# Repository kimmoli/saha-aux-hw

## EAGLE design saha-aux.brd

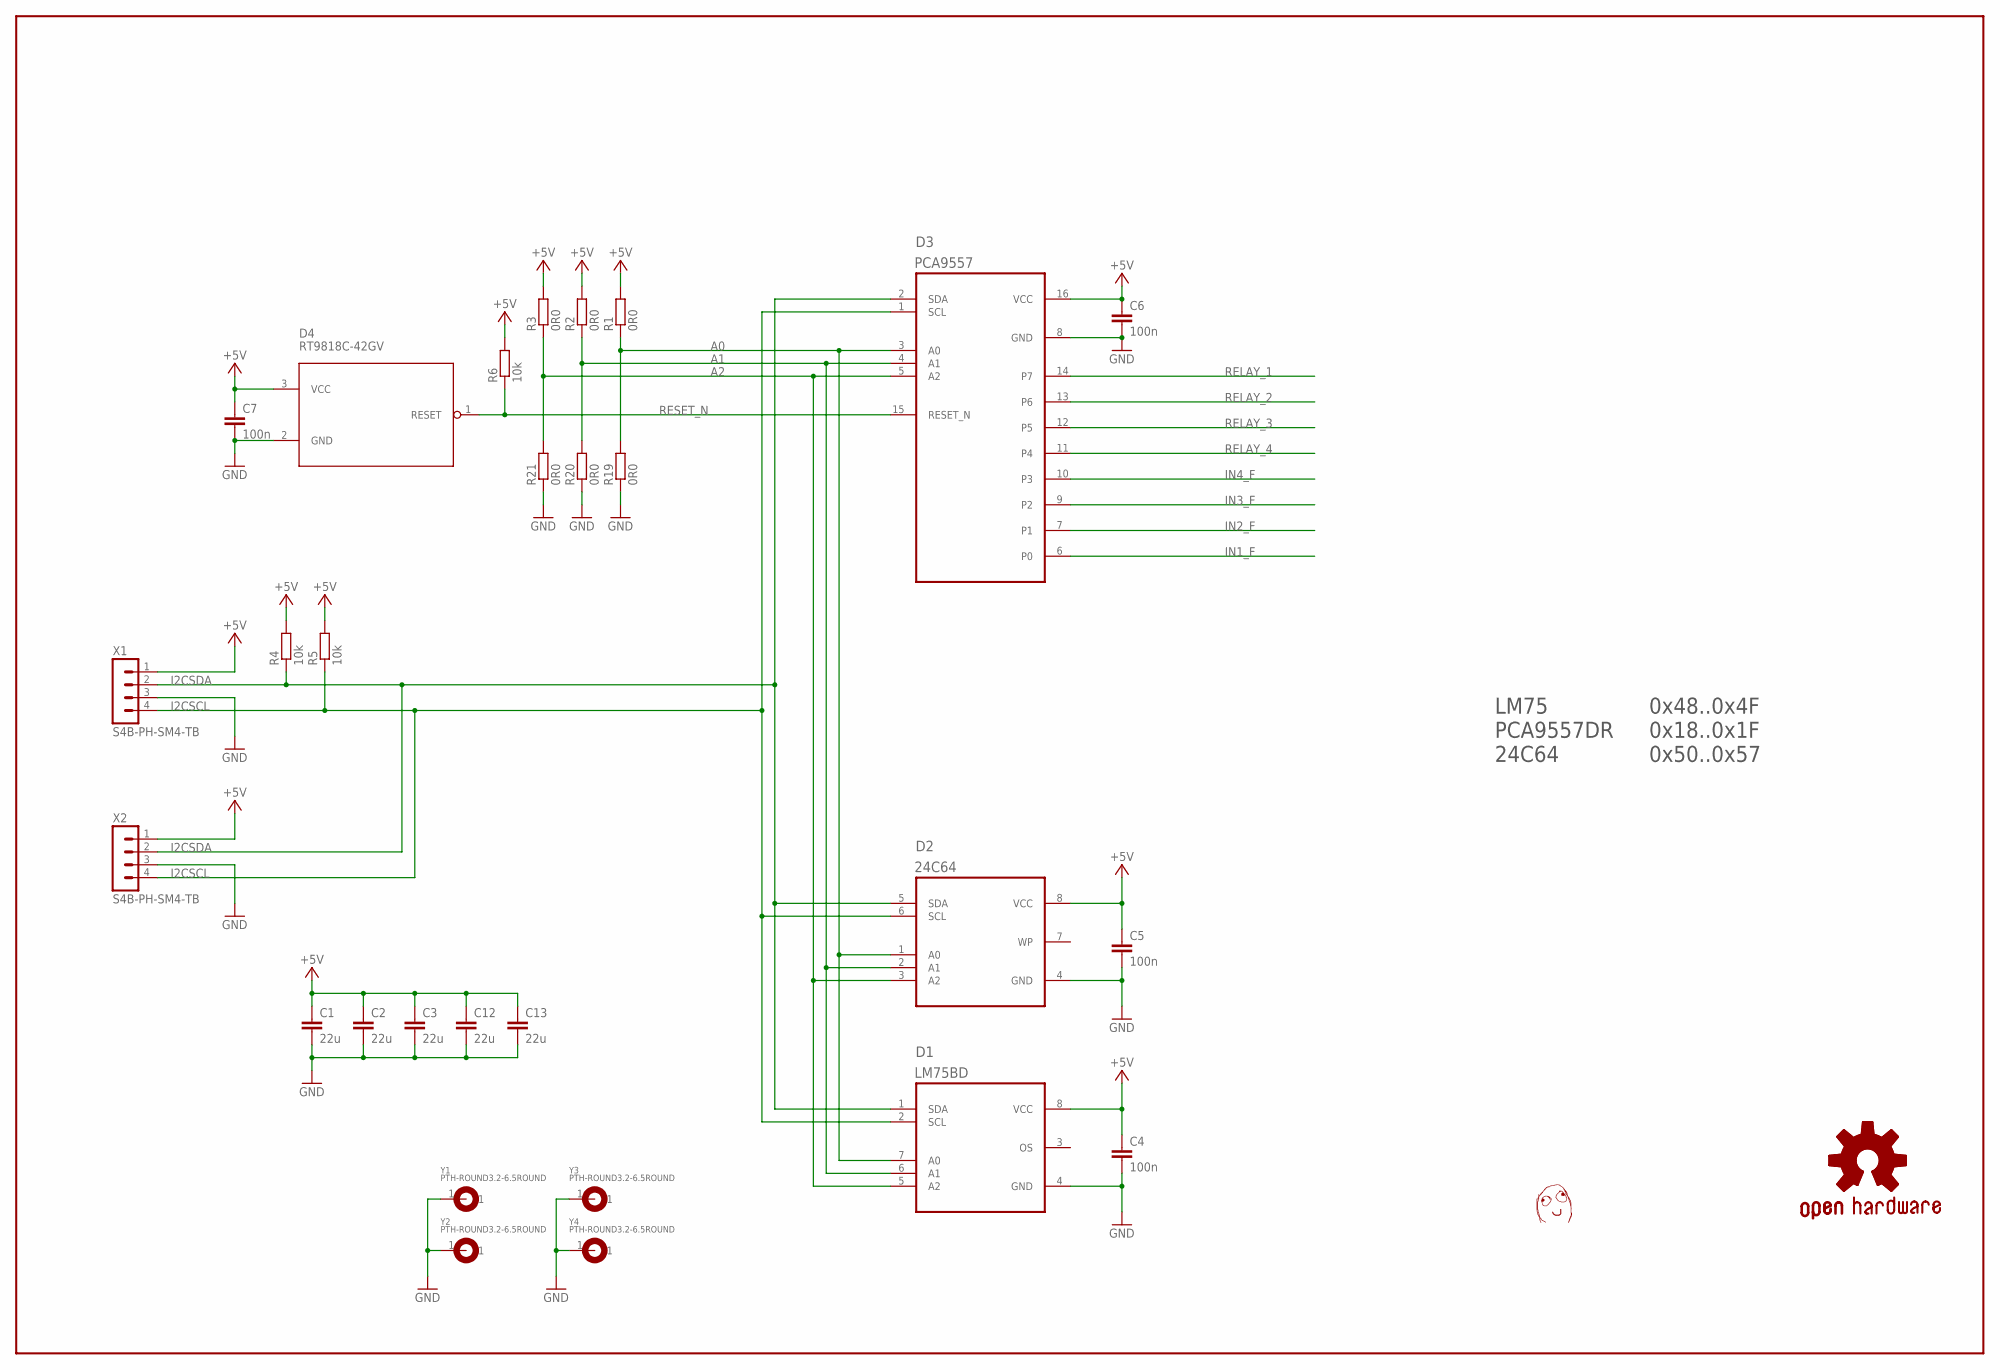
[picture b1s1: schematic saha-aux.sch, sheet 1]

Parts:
C1, C2, C3, C12, C13: 22u; C0805
C4, C5, C6, C7: 100n; C0603
D1: LM75BD; SOIC8-N
D2: 24C64; SOIC8-N
D3: PCA9557; SOIC16-N
D4: RT9818C-42GV; SOT23
R1, R2, R3, R19, R20, R21: 0R0; R0603
R4, R5, R6: 10k; R0603
U$1: DAFUG
X1, X2: S4B-PH-SM4-TB; JST-PH2.0-RA-4
Y1, Y2, Y3, Y4: PTH-ROUND3.2-6.5ROUND; EKE_PTH-3.2-6.5

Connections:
+5V: C1.1, C2.1, C3.1, C4.1, C5.1, C6.1, C7.1, C12.1, C13.1, D1.8 (VCC), D2.8 (VCC), D3.16 (VCC), D4.3 (VCC), R1.2, R2.2, R3.2, R4.2, R5.2, R6.2, X1.1, X2.1; also elsewhere on the board
A0: D1.7 (A0), D2.1 (A0), D3.3 (A0), R1.1, R19.2
A1: D1.6 (A1), D2.2 (A1), D3.4 (A1), R2.1, R20.2
A2: D1.5 (A2), D2.3 (A2), D3.5 (A2), R3.1, R21.2
GND: C1.2, C2.2, C3.2, C4.2, C5.2, C6.2, C7.2, C12.2, C13.2, D1.4 (GND), D2.4 (GND), D3.8 (GND), D4.2 (GND), R19.1, R20.1, R21.1, X1.3, X2.3, Y1.1, Y2.1, Y3.1, Y4.1; also elsewhere on the board
I2CSCL: D1.2 (SCL), D2.6 (SCL), D3.1 (SCL), R5.1, X1.4, X2.4
I2CSDA: D1.1 (SDA), D2.5 (SDA), D3.2 (SDA), R4.1, X1.2, X2.2
IN1_F: D3.6 (P0); also elsewhere on the board
IN2_F: D3.7 (P1); also elsewhere on the board
IN3_F: D3.9 (P2); also elsewhere on the board
IN4_F: D3.10 (P3); also elsewhere on the board
RELAY_1: D3.14 (P7); also elsewhere on the board
RELAY_2: D3.13 (P6); also elsewhere on the board
RELAY_3: D3.12 (P5); also elsewhere on the board
RELAY_4: D3.11 (P4); also elsewhere on the board
RESET_N: D3.15 (RESET_N), D4.1 (RESET), R6.1

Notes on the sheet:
LM75 PCA9557DR 24C64
0x48..0x4F 0x18..0x1F 0x50..0x57

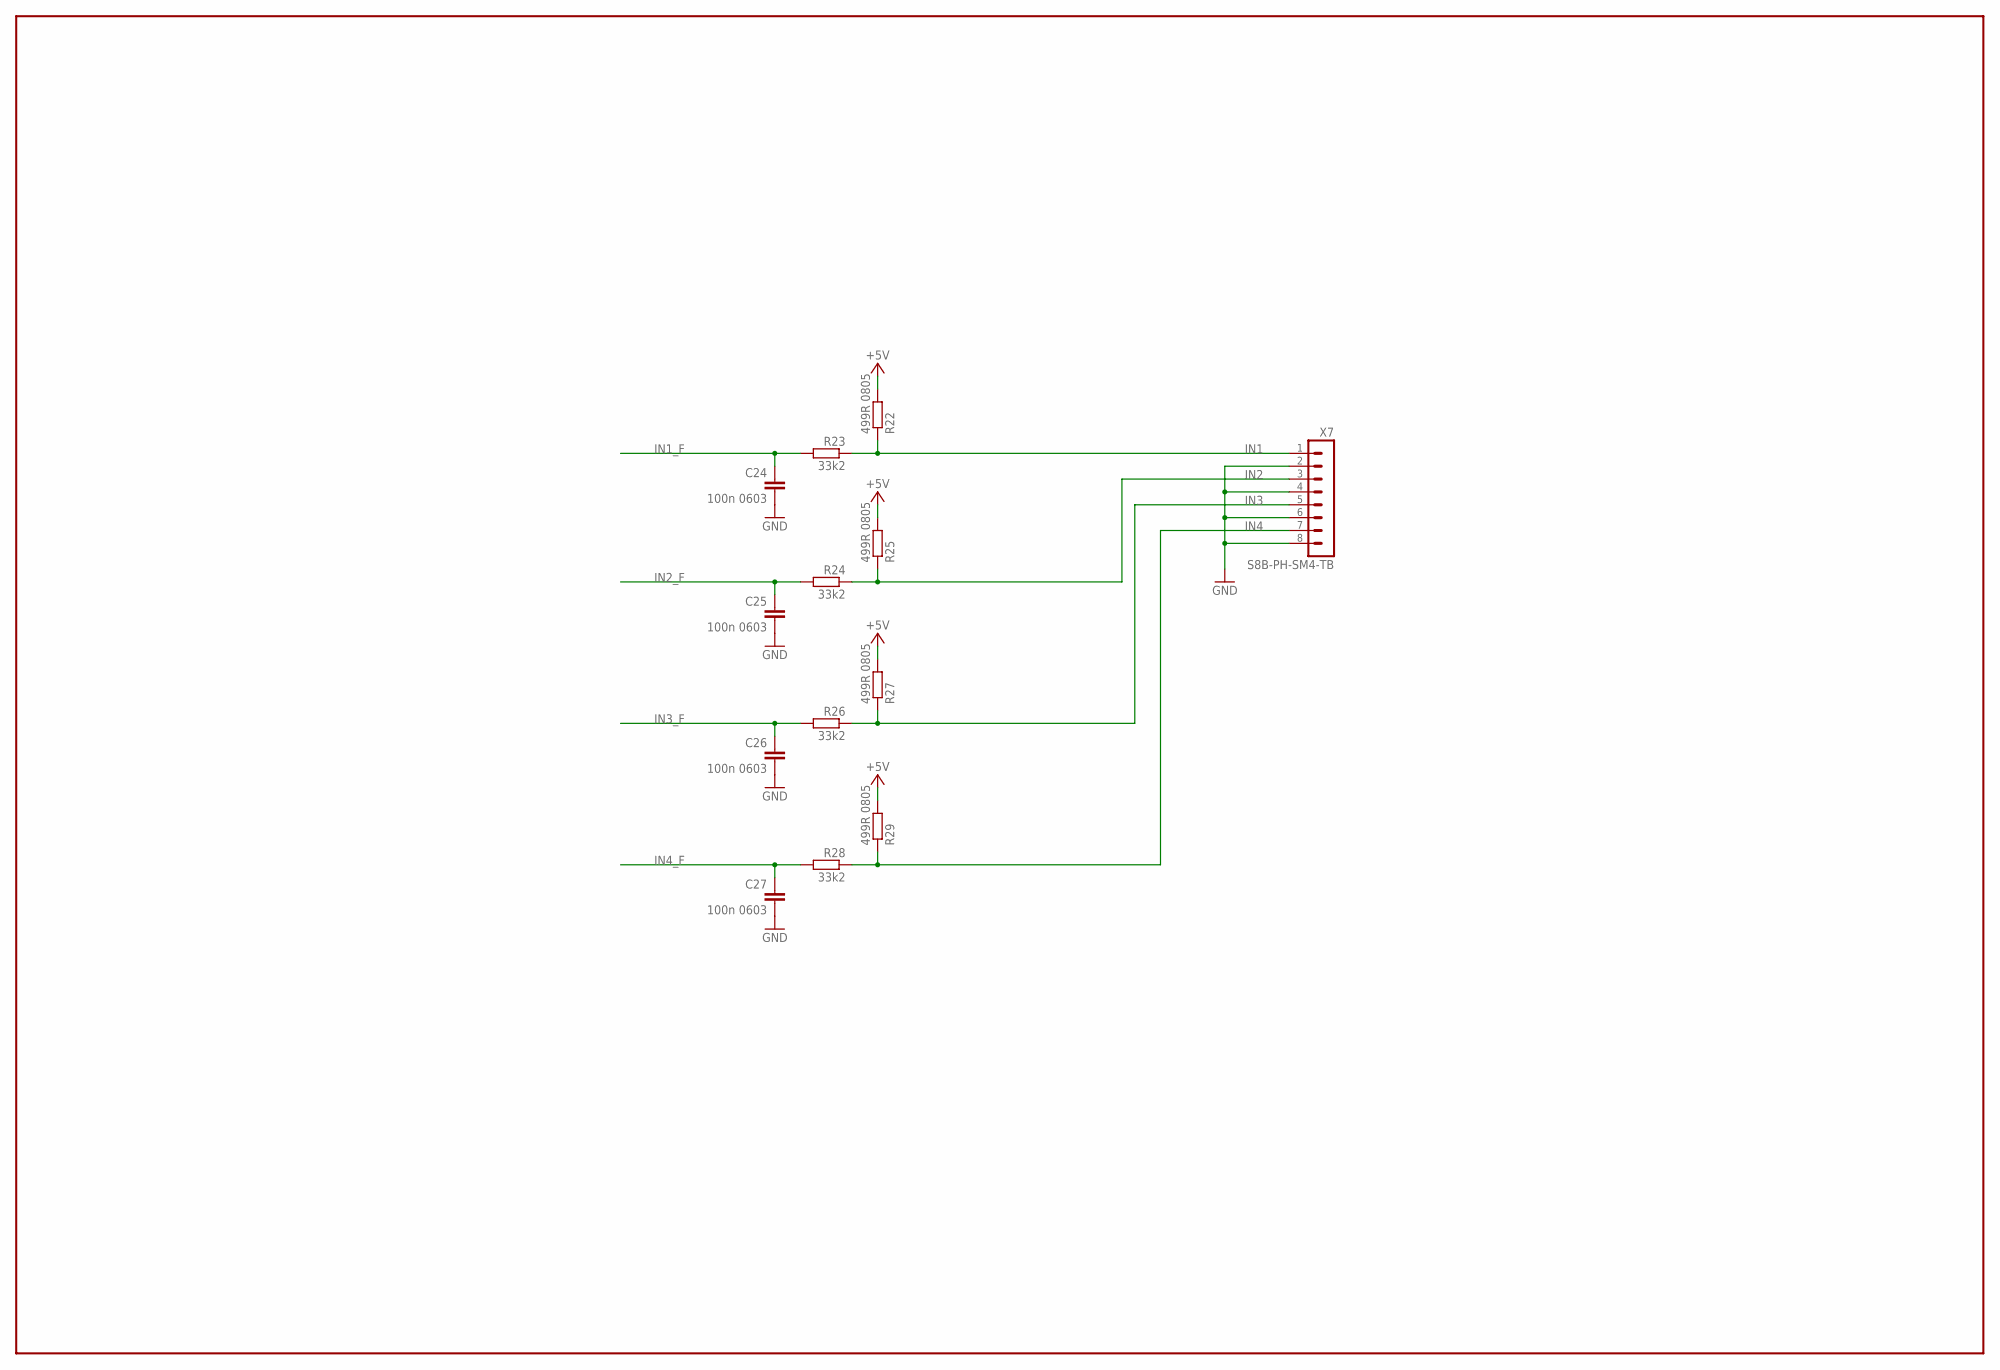
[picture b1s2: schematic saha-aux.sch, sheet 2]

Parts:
C24, C25, C26, C27: 100n 0603; C0603
R22, R25, R27, R29: 499R 0805; R0805
R23, R24, R26, R28: 33k2; R0603
X7: S8B-PH-SM4-TB; JST-PH2.0-RA-8

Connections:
+5V: R22.2, R25.2, R27.2, R29.2; also elsewhere on the board
GND: C24.2, C25.2, C26.2, C27.2, X7.2, X7.4, X7.6, X7.8; also elsewhere on the board
IN1: R22.1, R23.1, X7.1
IN1_F: C24.1, R23.2; also elsewhere on the board
IN2: R24.1, R25.1, X7.3
IN2_F: C25.1, R24.2; also elsewhere on the board
IN3: R26.1, R27.1, X7.5
IN3_F: C26.1, R26.2; also elsewhere on the board
IN4: R28.1, R29.1, X7.7
IN4_F: C27.1, R28.2; also elsewhere on the board

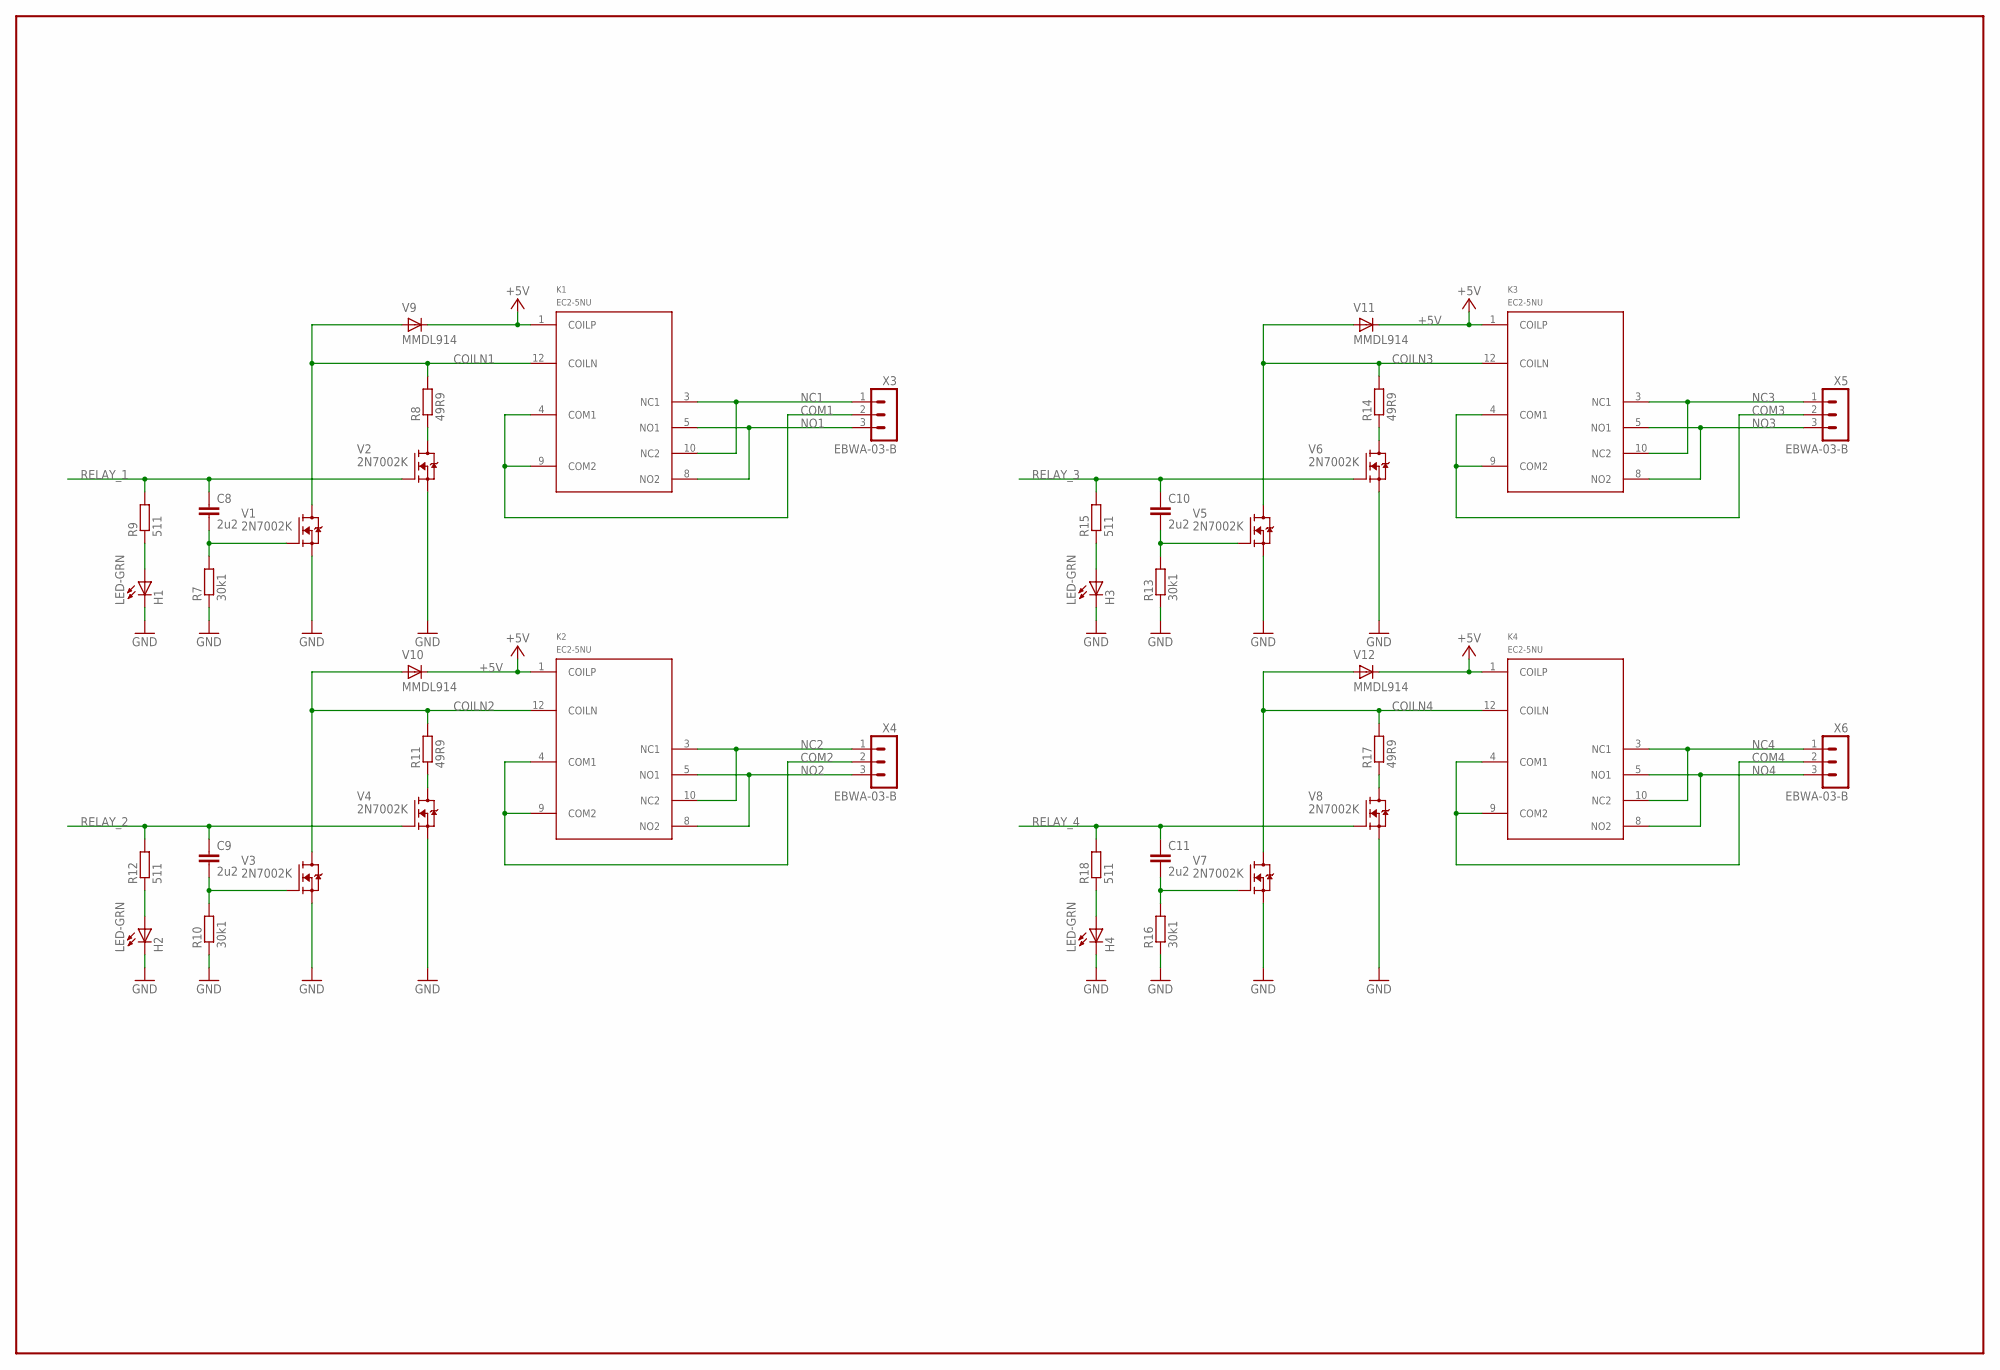
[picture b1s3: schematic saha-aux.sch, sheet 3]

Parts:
C8, C9, C10, C11: 2u2; C0603
H1, H2, H3, H4: LED-GRN; CHIP-LED0603
K1, K2, K3, K4: EC2-5NU; EC2
R7, R10, R13, R16: 30k1; R0603
R8, R11, R14, R17: 49R9; R0805
R9, R12, R15, R18: 511; R0603
V1, V2, V3, V4, V5, V6, V7, V8: 2N7002K; SOT23
V9, V10, V11, V12: MMDL914; SOD-323
X3, X4, X5, X6: EBWA-03-B; RUUVILIITIN381-3

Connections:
+5V: K1.1 (COILP), K2.1 (COILP), K3.1 (COILP), K4.1 (COILP), V9.C, V10.C, V11.C, V12.C; also elsewhere on the board
COILN1: K1.12 (COILN), R8.2, V1.3 (D), V9.A
COILN2: K2.12 (COILN), R11.2, V3.3 (D), V10.A
COILN3: K3.12 (COILN), R14.2, V5.3 (D), V11.A
COILN4: K4.12 (COILN), R17.2, V7.3 (D), V12.A
COM1: K1.4 (COM1), K1.9 (COM2), X3.2
COM2: K2.4 (COM1), K2.9 (COM2), X4.2
COM3: K3.4 (COM1), K3.9 (COM2), X5.2
COM4: K4.4 (COM1), K4.9 (COM2), X6.2
GND: H1.C, H2.C, H3.C, H4.C, R7.1, R10.1, R13.1, R16.1, V1.2 (S), V2.2 (S), V3.2 (S), V4.2 (S), V5.2 (S), V6.2 (S), V7.2 (S), V8.2 (S); also elsewhere on the board
unnamed: H1.A, R9.1
unnamed: C8.2, R7.2, V1.1 (G)
unnamed: R8.1, V2.3 (D)
unnamed: C9.2, R10.2, V3.1 (G)
unnamed: R11.1, V4.3 (D)
unnamed: H2.A, R12.1
unnamed: C10.2, R13.2, V5.1 (G)
unnamed: R14.1, V6.3 (D)
unnamed: H3.A, R15.1
unnamed: C11.2, R16.2, V7.1 (G)
unnamed: R17.1, V8.3 (D)
unnamed: H4.A, R18.1
NC1: K1.3 (NC1), K1.10 (NC2), X3.1
NC2: K2.3 (NC1), K2.10 (NC2), X4.1
NC3: K3.3 (NC1), K3.10 (NC2), X5.1
NC4: K4.3 (NC1), K4.10 (NC2), X6.1
NO1: K1.5 (NO1), K1.8 (NO2), X3.3
NO2: K2.5 (NO1), K2.8 (NO2), X4.3
NO3: K3.5 (NO1), K3.8 (NO2), X5.3
NO4: K4.5 (NO1), K4.8 (NO2), X6.3
RELAY_1: C8.1, R9.2, V2.1 (G); also elsewhere on the board
RELAY_2: C9.1, R12.2, V4.1 (G); also elsewhere on the board
RELAY_3: C10.1, R15.2, V6.1 (G); also elsewhere on the board
RELAY_4: C11.1, R18.2, V8.1 (G); also elsewhere on the board

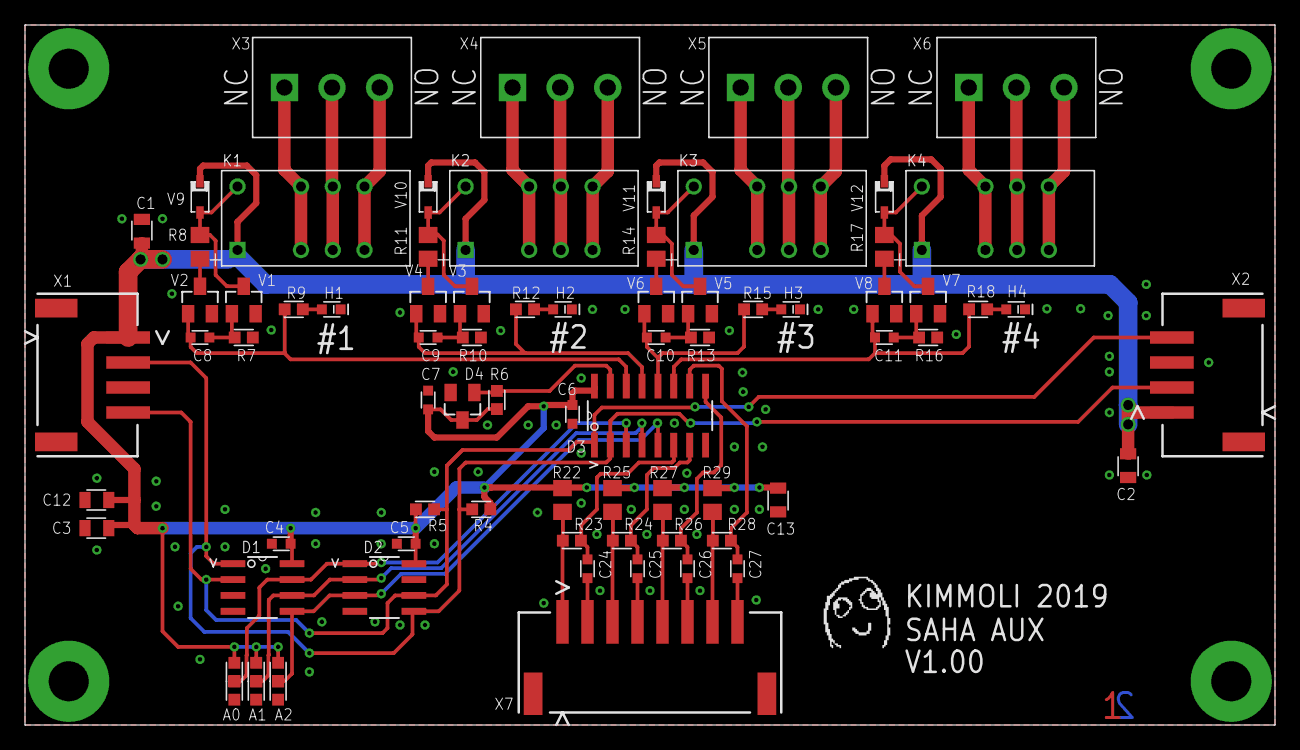
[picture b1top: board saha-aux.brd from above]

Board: 2 copper layers, 100.0 x 56.0 mm, 82 parts (0 on the bottom side), 48 nets.

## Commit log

2019-09-11 initial
2019-09-14 placement round 1
2019-09-14 finished v1.00
2019-09-14 remove bottom silk
